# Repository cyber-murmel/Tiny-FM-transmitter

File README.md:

# Tiny-FM-transmitter

## BOM

Every passive component is 0805.

| Reference  | Value                         | Shop Link                                                  |
|------------|-------------------------------|------------------------------------------------------------|
| R1, R2, R3 | 1k                            |   |
| RV1        | 10k 3*3                       | [Taobao](https://item.taobao.com/item.htm?id=562183017821) |
| C1, C2     | 1uF                           | [Taobao](https://item.taobao.com/item.htm?id=551324130901) |
| C3, C4, C5 | 1nF NP0                       | [Taobao](https://item.taobao.com/item.htm?id=549142254986) |
| L1         | 390nH                         | [Taobao](https://item.taobao.com/item.htm?id=553342609305) |
| U1         | MAX2606                       | [Taobao](https://item.taobao.com/item.htm?id=562831308172) |
| U2         | AP2204K-2.8                   | [Taobao](https://item.taobao.com/item.htm?id=38658505879) |
| MK1        | PMO-4530PN-47UQ or equivalent | [Taobao](https://item.taobao.com/item.htm?id=522576248784) |
| BT1        | Keystone 3034                 | [Taobao](https://item.taobao.com/item.htm?id=564362395469) |

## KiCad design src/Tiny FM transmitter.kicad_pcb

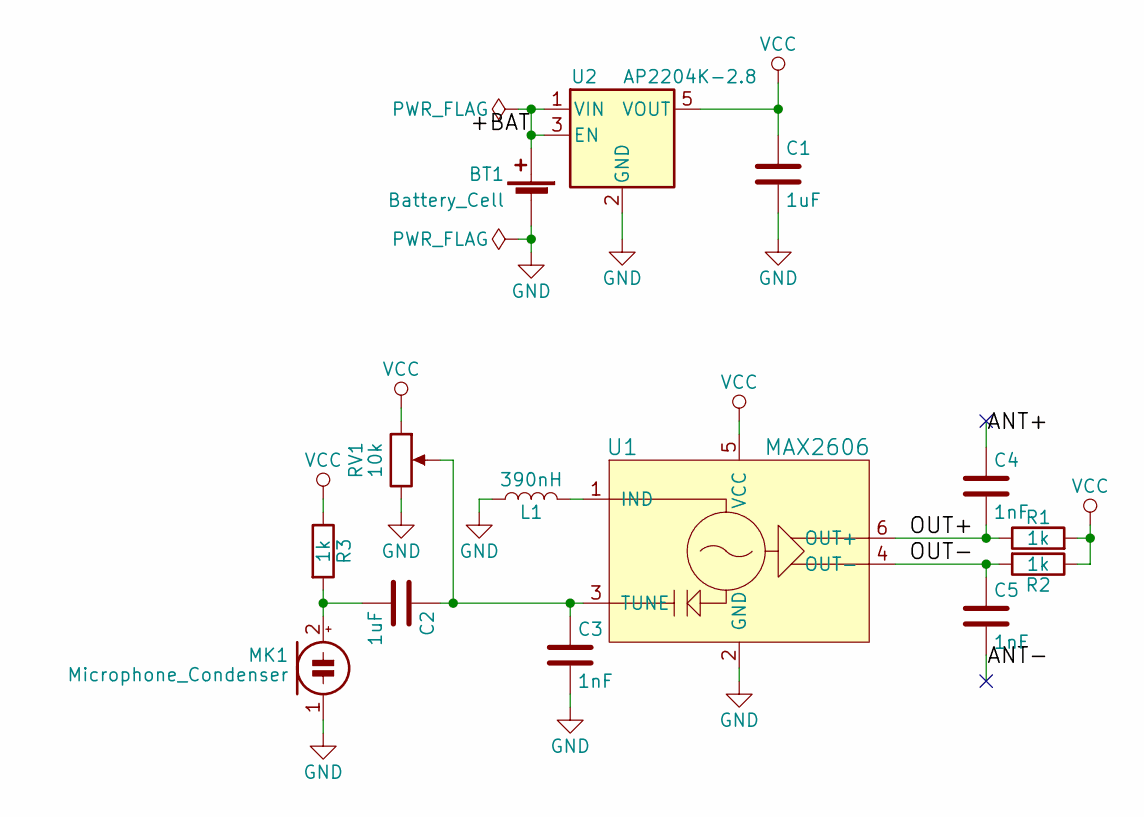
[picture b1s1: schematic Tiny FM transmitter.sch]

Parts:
BT1: Battery_Cell; Keystone_3034_1x20mm-CoinCell
C1, C2: 1uF; C_0603_HandSoldering
C3, C4, C5: 1nF; C_0603_HandSoldering
L1: 390nH; L_0603_HandSoldering
MK1: Microphone_Condenser; HM4522P-423-G
R1, R2, R3: 1k; R_0603_HandSoldering
RV1: 10k; Potentiometer_Trimmer-EVM3E
U1: MAX2606; SOT-23-6_Handsoldering
U2: AP2204K-2.8; SOT-23-5_HandSoldering

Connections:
/+BAT: BT1.1 (+), U2.1 (VIN), U2.3 (EN)
/ANT+: C4.1
/ANT-: C5.2
/OUT+: C4.2, R1.1, U1.6 (OUT+)
/OUT-: C5.1, R2.2, U1.4 (OUT-)
GND: BT1.2 (-), C1.2, C3.2, L1.1, MK1.1 (-), RV1.3, U1.2 (GND), U2.2 (GND)
unnamed: C2.1, C3.1, RV1.2, U1.3 (TUNE)
unnamed: C2.2, MK1.2 (+), R3.2
unnamed: L1.2, U1.1 (IND)
VCC: C1.1, R1.2, R2.1, R3.1, RV1.1, U1.5 (VCC), U2.5 (VOUT)

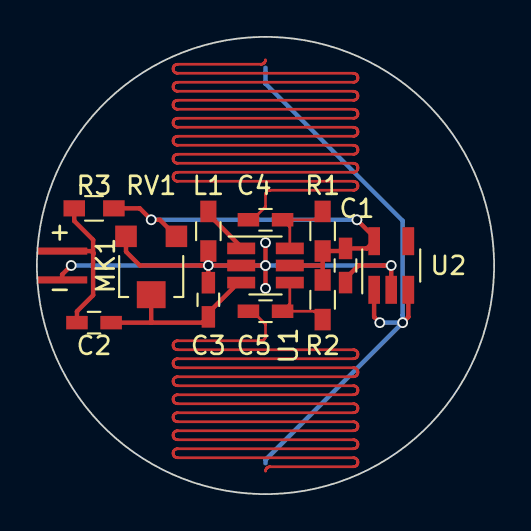
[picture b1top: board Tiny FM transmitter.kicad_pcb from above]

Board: 2 copper layers, 25.4 x 25.4 mm, 14 parts (1 on the bottom side), 8 nets.

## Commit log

2018-02-22 finished routing. successfull DRC
2018-02-22 added rendered image
